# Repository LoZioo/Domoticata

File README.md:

# Domoticata
Custom domotic home system.

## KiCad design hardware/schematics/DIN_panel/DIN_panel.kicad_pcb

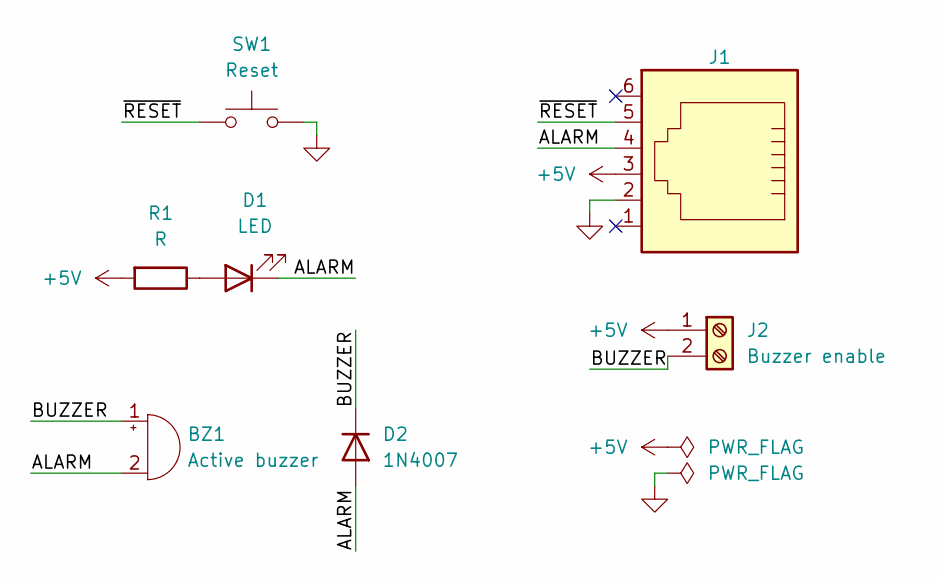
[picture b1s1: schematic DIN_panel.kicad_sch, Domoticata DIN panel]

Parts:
BZ1: Active buzzer; Buzzer_12x9.5RM7.6
D1: LED; LED_D5.0mm
D2: 1N4007; D_DO-41_SOD81_P7.62mm_Horizontal
J1: 6P6C; RJ25_Wayconn_MJEA-660X1_Horizontal
J2: Buzzer enable; TerminalBlock_4Ucon_1x02_P3.50mm_Horizontal
R1: R; R_Axial_DIN0207_L6.3mm_D2.5mm_P7.62mm_Horizontal
SW1: Reset; SW_PUSH_6mm_H5mm

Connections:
+5V: J1.3, J2.1, R1.2
/ALARM: BZ1.2 (-), D1.1 (K), D2.2 (A), J1.4
/BUZZER: BZ1.1 (+), D2.1 (K), J2.2
/~RESET: J1.5, SW1.1
GND: J1.2, SW1.2
unnamed: D1.2 (A), R1.1

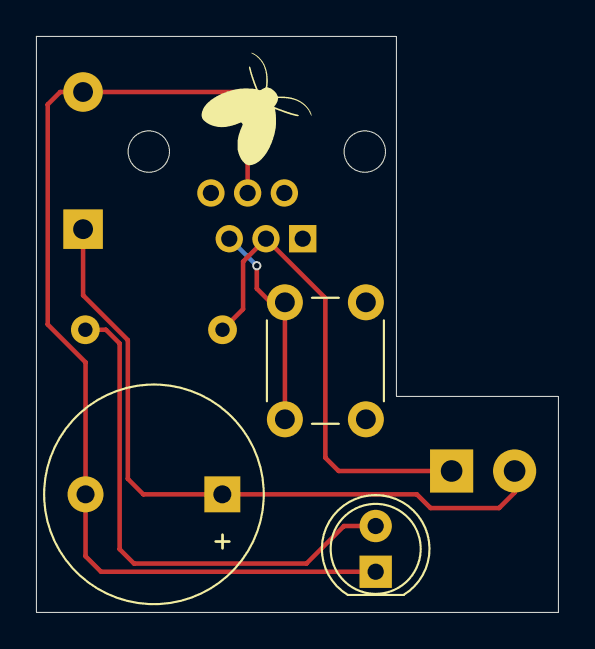
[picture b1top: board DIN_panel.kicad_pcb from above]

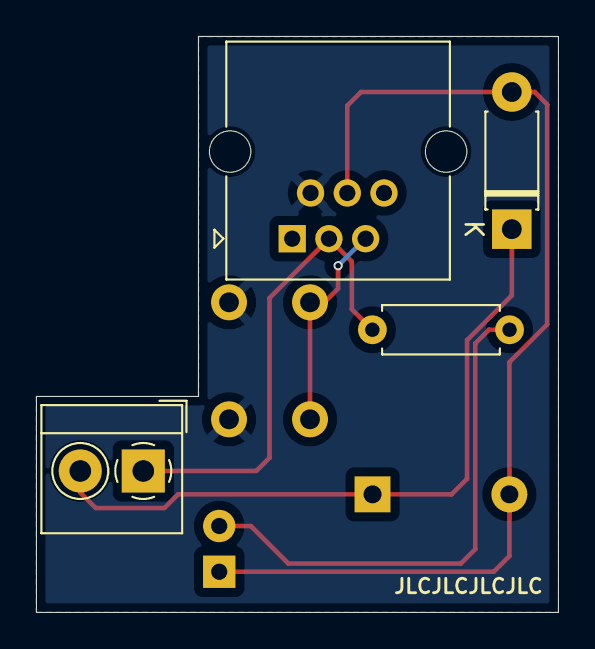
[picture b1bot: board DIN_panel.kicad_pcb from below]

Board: 2 copper layers, 29.0 x 32.0 mm, 7 parts (4 on the bottom side), 6 nets.

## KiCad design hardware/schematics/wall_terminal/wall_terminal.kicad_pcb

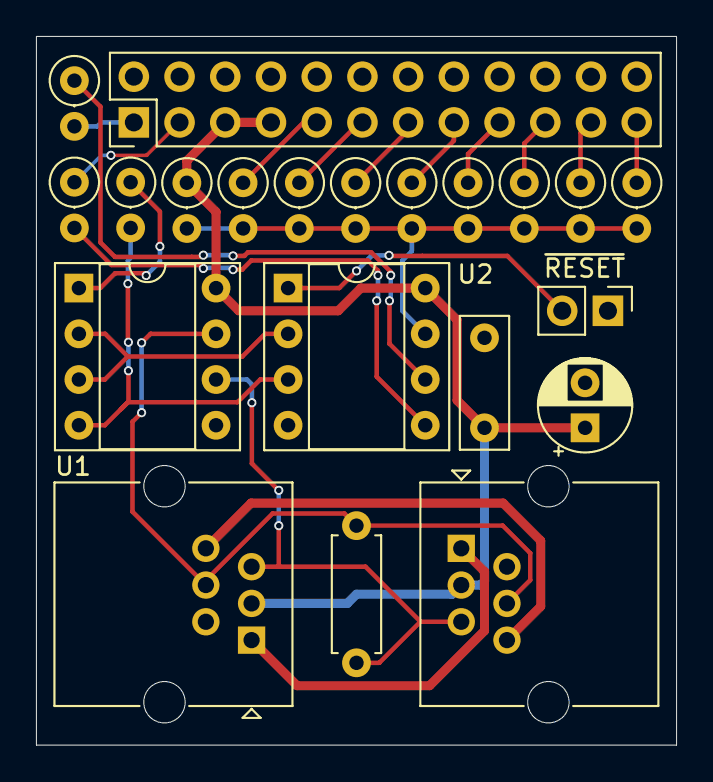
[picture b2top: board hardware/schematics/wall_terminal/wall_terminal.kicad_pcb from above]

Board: 2 copper layers, 35.6 x 39.4 mm, 21 parts (0 on the bottom side), 23 nets.

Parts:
C1: 10uF; CP_Radial_D5.0mm_P2.50mm
C2: 100nF; C_Rect_L7.2mm_W2.5mm_P5.00mm_FKS2_FKP2_MKS2_MKP2
J1: Reset; PinHeader_1x02_P2.54mm_Vertical
J2: Conn_02x12_Odd_Even; PinHeader_2x12_P2.54mm_Vertical
J3, J4: 6P6C; RJ25_Wayconn_MJEA-660X1_Horizontal
R1, R2, R3, R4, R5, R6, R7, R8, R9, R10, R11: R; R_Axial_DIN0207_L6.3mm_D2.5mm_P2.54mm_Vertical
R12: 1k; R_Axial_DIN0207_L6.3mm_D2.5mm_P2.54mm_Vertical
R13: 120; R_Axial_DIN0207_L6.3mm_D2.5mm_P7.62mm_Horizontal
U1: MAX487E; DIP-8_W7.62mm_Socket
U2: ATtiny13A-P; DIP-8_W7.62mm_Socket

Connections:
+5V: C1.1, C2.1, J2.5, J2.7, J3.3, J4.3, R11.1, U1.8 (VCC), U2.8 (VCC)
/BUS_SHORT_1: J3.1, J4.1
/BUS_SHORT_6: J3.6, J4.6
/IN/ADC: R3.2, R4.2, R5.2, R6.2, R7.2, R8.2, R9.2, R10.2, R11.2, U2.7 (PB2)
/IN/S1: J2.23, R3.1
/IN/S2: J2.21, R4.1
/IN/S3: J2.19, R5.1
/IN/S4: J2.17, R6.1
/IN/S5: J2.15, R7.1
/IN/S6: J2.13, R8.1
/IN/S7: J2.11, R9.1
/IN/S8: J2.9, R10.1
/MCU/DE/~RE: U1.2 (~RE), U1.3 (DE), U2.2 (PB3)
/MCU/PWM_A: R1.2, U2.5 (PB0)
/MCU/PWM_B: R2.1, U2.6 (PB1)
/MCU/RX/TX: R12.2, U1.4 (DI), U2.3 (PB4)
/MCU/~RST: J1.2, U2.1 (~RESET/PB5)
/RS485_A: J3.5, J4.5, R13.1, U1.6 (A)
/RS485_B: J3.4, J4.4, R13.2, U1.7 (B)
GND: C1.2, C2.2, J1.1, J2.2, J2.4, J2.6, J2.8, J2.10, J2.12, J2.14, J2.16, J2.18, J2.20, J2.22, J2.24, J3.2, J4.2, U1.5 (GND), U2.4 (GND)
unnamed: J2.1, R2.2
unnamed: J2.3, R1.1
unnamed: R12.1, U1.1 (RO)

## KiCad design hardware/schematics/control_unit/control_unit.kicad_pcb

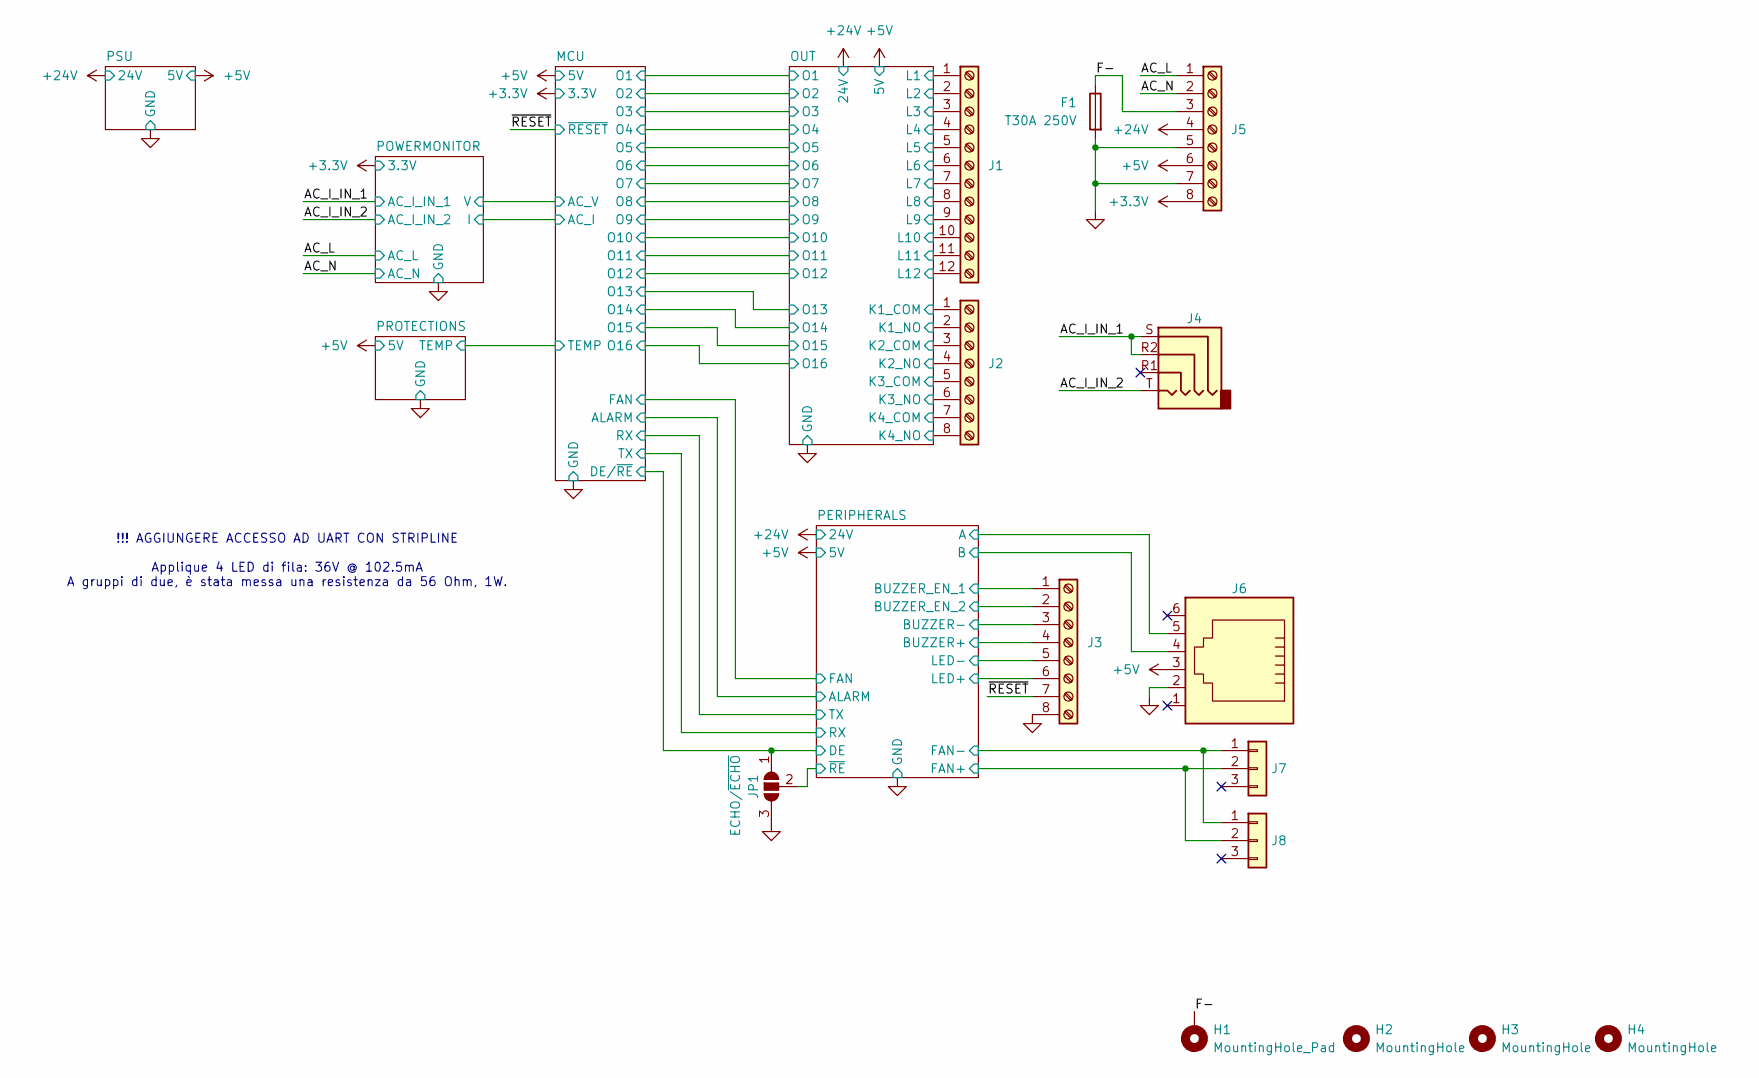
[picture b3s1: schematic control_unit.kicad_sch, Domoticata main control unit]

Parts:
F1: T30A 250V; Fuseholder_Clip-6.3x32mm_Littelfuse_102_Inline_P34.21x7.62m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
H1: MountingHole_Pad; MountingHole_4.5mm_Pad_TopBottom
H2, H3, H4: MountingHole; MountingHole_4.5mm_Pad_TopBottom
J1: Screw_Terminal_01x12; PhoenixContact_MCV_1,5_12-G-3.81_1x12_P3.81mm_D1.4mm_Vertic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
J2, J3, J5: Screw_Terminal_01x08; PhoenixContact_MCV_1,5_8-G-3.81_1x08_P3.81mm_D1.4mm_Vertical
J4: AudioJack4; SCT013
J6: 6P6C; RJ25_Wayconn_MJEA-660X1_Horizontal
J7, J8: Conn_01x03_Pin; FanPinHeader_1x03_P2.54mm_Vertical
JP1: ECHO/~{ECHO}; SolderJumper-3_P1.3mm_Open_Pad1.0x1.5mm

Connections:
+3.3V: J5.8; also elsewhere on the board
+5V: J3.4, J3.6, J5.6, J6.3; also elsewhere on the board
+24V: J5.4, J7.2, J8.2; also elsewhere on the board
/AC_I_IN_1: J4.R2, J4.S; also elsewhere on the board
/AC_I_IN_2: J4.T; also elsewhere on the board
/AC_L: J5.1; also elsewhere on the board
/AC_N: J5.2; also elsewhere on the board
/F-: F1.1, H1.1, J5.3
/MCU/DE/~RE: JP1.1 (A); also elsewhere on the board
/OUT/K1_COM: J2.1; also elsewhere on the board
/OUT/K1_NO: J2.2; also elsewhere on the board
/OUT/K2_COM: J2.3; also elsewhere on the board
/OUT/K2_NO: J2.4; also elsewhere on the board
/OUT/K3_COM: J2.5; also elsewhere on the board
/OUT/K3_NO: J2.6; also elsewhere on the board
/OUT/K4_COM: J2.7; also elsewhere on the board
/OUT/K4_NO: J2.8; also elsewhere on the board
/OUT/L1: J1.1; also elsewhere on the board
/OUT/L2: J1.2; also elsewhere on the board
/OUT/L3: J1.3; also elsewhere on the board
/OUT/L4: J1.4; also elsewhere on the board
/OUT/L5: J1.5; also elsewhere on the board
/OUT/L6: J1.6; also elsewhere on the board
/OUT/L7: J1.7; also elsewhere on the board
/OUT/L8: J1.8; also elsewhere on the board
/OUT/L9: J1.9; also elsewhere on the board
/OUT/L10: J1.10; also elsewhere on the board
/OUT/L11: J1.11; also elsewhere on the board
/OUT/L12: J1.12; also elsewhere on the board
/PERIPHERALS/A: J6.5; also elsewhere on the board
/PERIPHERALS/B: J6.4; also elsewhere on the board
/PERIPHERALS/BUZZER-: J3.1, J3.3
/PERIPHERALS/BUZZER_EN_2: J3.2; also elsewhere on the board
/PERIPHERALS/FAN-: J7.1, J8.1; also elsewhere on the board
/PERIPHERALS/LED-: J3.5; also elsewhere on the board
/PERIPHERALS/~RE: JP1.2 (C); also elsewhere on the board
/~RESET: J3.7; also elsewhere on the board
GND: F1.2, J3.8, J5.5, J5.7, J6.2, JP1.3 (B); also elsewhere on the board

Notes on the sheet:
!!! AGGIUNGERE ACCESSO AD UART CON STRIPLINE Applique 4 LED di fila: 36V @ 102.5mA A gruppi di due, è stata messa una resistenza da 56 Ohm, 1W.

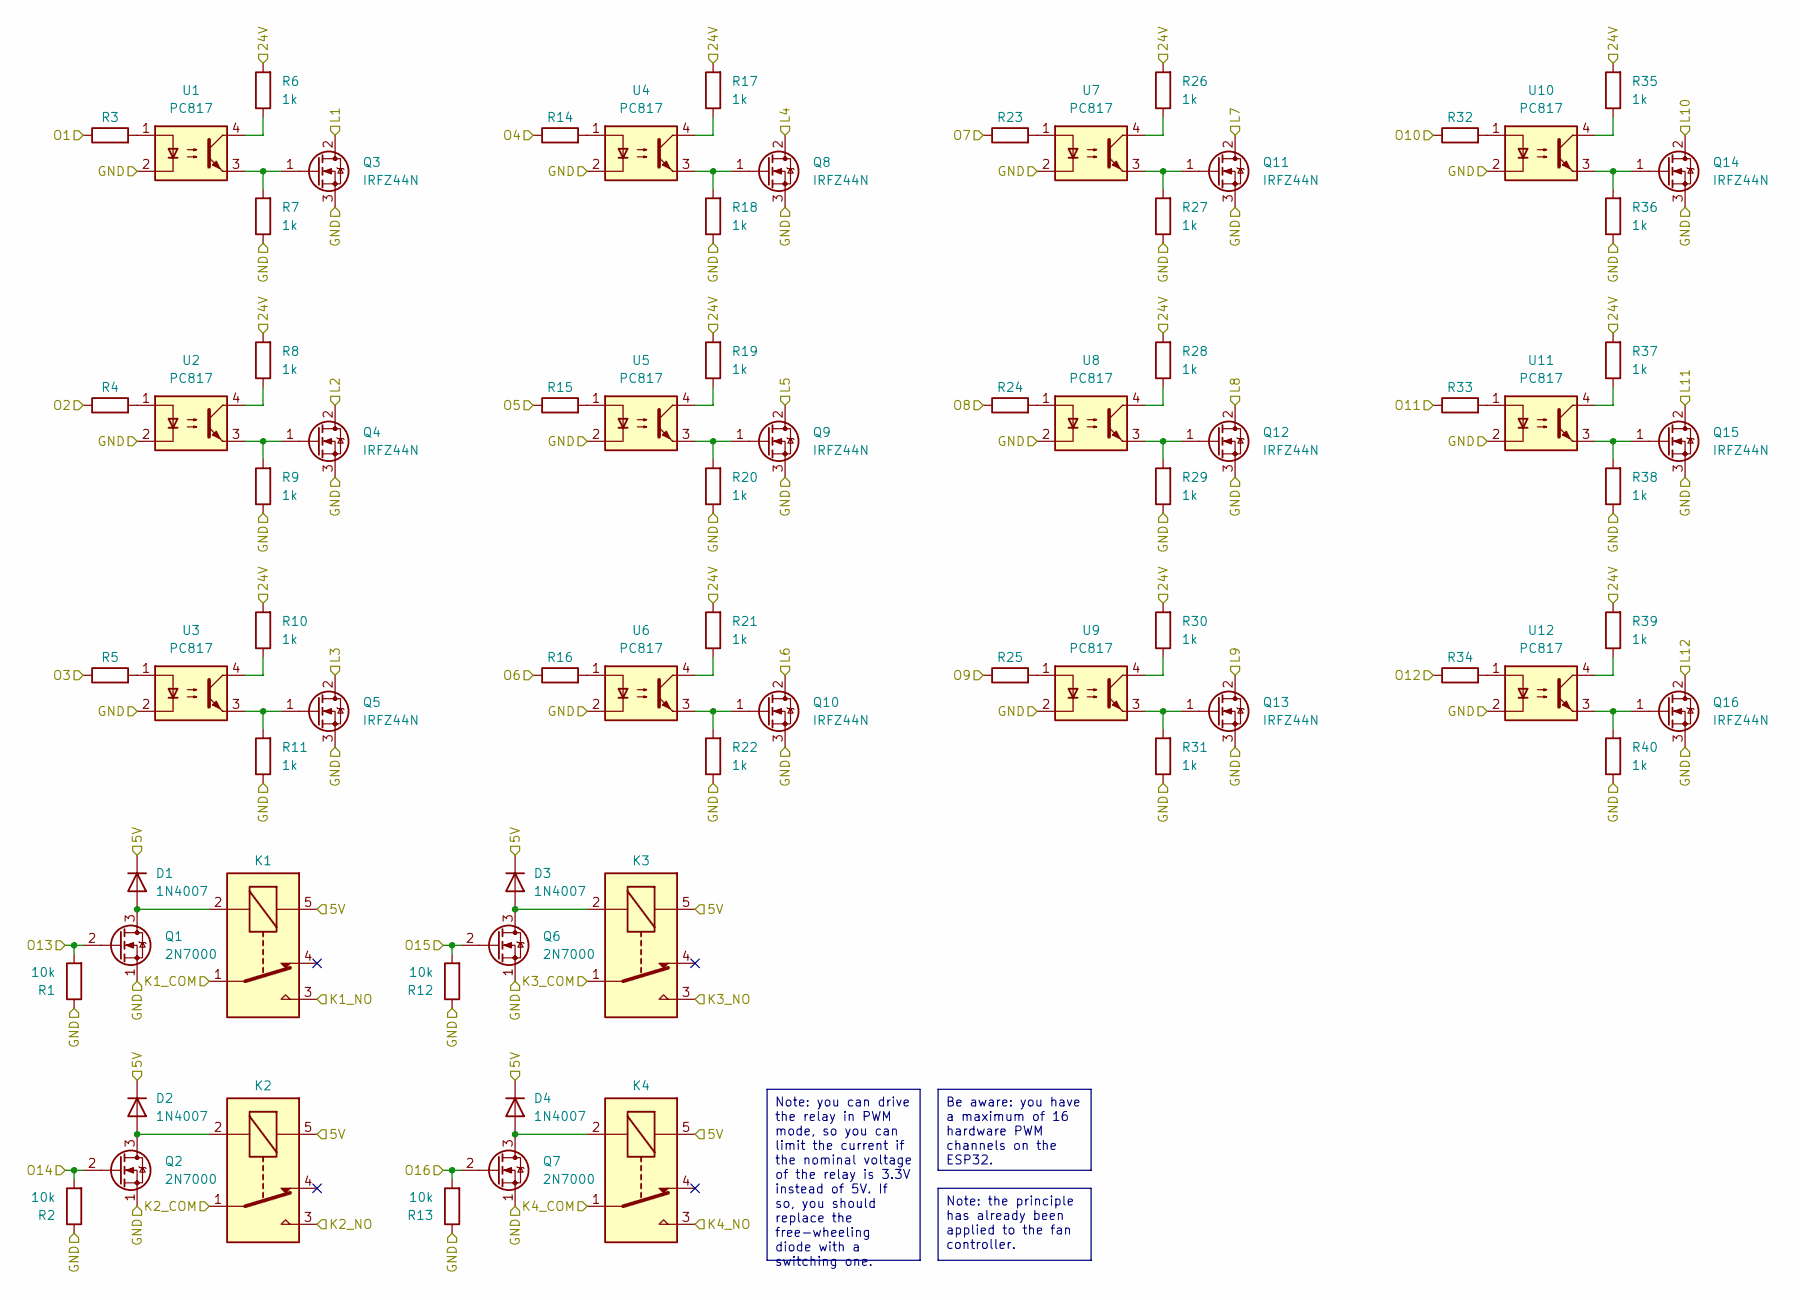
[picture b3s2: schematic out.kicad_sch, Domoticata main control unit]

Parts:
D1, D2, D3, D4: 1N4007; D_DO-41_SOD81_P7.62mm_Horizontal
K1, K2, K3, K4: Relay_SPDT; Relay_SPDT_Omron-G5LE-1
Q1, Q2, Q6, Q7: 2N7000; TO-92_Inline
Q3, Q4, Q5, Q8, Q9, Q10, Q11, Q12, Q13, Q14, Q15, Q16: IRFZ44N; TO-220-3_Vertical
R1, R2, R12, R13: 10k; R_Axial_DIN0207_L6.3mm_D2.5mm_P7.62mm_Horizontal
R3, R4, R5, R14, R15, R16, R23, R24, R25, R32, R33, R34: R; R_Axial_DIN0207_L6.3mm_D2.5mm_P7.62mm_Horizontal
R6, R7, R8, R9, R10, R11, R17, R18, R19, R20, R21, R22, R26, R27, R28, R29, R30, R31, R35, R36, R37, R38, R39, R40: 1k; R_Axial_DIN0207_L6.3mm_D2.5mm_P7.62mm_Horizontal
U1, U2, U3, U4, U5, U6, U7, U8, U9, U10, U11, U12: PC817; DIP-4_W7.62mm

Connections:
+5V: D1.1 (K), D2.1 (K), D3.1 (K), D4.1 (K), K1.5, K2.5, K3.5, K4.5; also elsewhere on the board
+24V: R6.2, R8.2, R10.2, R17.2, R19.2, R21.2, R26.2, R28.2, R30.2, R35.2, R37.2, R39.2; also elsewhere on the board
/MCU/O1: R3.1; also elsewhere on the board
/MCU/O2: R4.1; also elsewhere on the board
/MCU/O3: R5.1; also elsewhere on the board
/MCU/O4: R14.1; also elsewhere on the board
/MCU/O5: R15.1; also elsewhere on the board
/MCU/O6: R16.1; also elsewhere on the board
/MCU/O7: R23.1; also elsewhere on the board
/MCU/O8: R24.1; also elsewhere on the board
/MCU/O9: R25.1; also elsewhere on the board
/MCU/O10: R32.1; also elsewhere on the board
/MCU/O11: R33.1; also elsewhere on the board
/MCU/O12: R34.1; also elsewhere on the board
/MCU/O13: Q1.2 (G), R1.2; also elsewhere on the board
/MCU/O14: Q2.2 (G), R2.2; also elsewhere on the board
/MCU/O15: Q6.2 (G), R12.2; also elsewhere on the board
/MCU/O16: Q7.2 (G), R13.2; also elsewhere on the board
/OUT/K1_COM: K1.1; also elsewhere on the board
/OUT/K1_NO: K1.3; also elsewhere on the board
/OUT/K2_COM: K2.1; also elsewhere on the board
/OUT/K2_NO: K2.3; also elsewhere on the board
/OUT/K3_COM: K3.1; also elsewhere on the board
/OUT/K3_NO: K3.3; also elsewhere on the board
/OUT/K4_COM: K4.1; also elsewhere on the board
/OUT/K4_NO: K4.3; also elsewhere on the board
/OUT/L1: Q3.2 (D); also elsewhere on the board
/OUT/L2: Q4.2 (D); also elsewhere on the board
/OUT/L3: Q5.2 (D); also elsewhere on the board
/OUT/L4: Q8.2 (D); also elsewhere on the board
/OUT/L5: Q9.2 (D); also elsewhere on the board
/OUT/L6: Q10.2 (D); also elsewhere on the board
/OUT/L7: Q11.2 (D); also elsewhere on the board
/OUT/L8: Q12.2 (D); also elsewhere on the board
/OUT/L9: Q13.2 (D); also elsewhere on the board
/OUT/L10: Q14.2 (D); also elsewhere on the board
/OUT/L11: Q15.2 (D); also elsewhere on the board
/OUT/L12: Q16.2 (D); also elsewhere on the board
GND: Q1.1 (S), Q2.1 (S), Q3.3 (S), Q4.3 (S), Q5.3 (S), Q6.1 (S), Q7.1 (S), Q8.3 (S), Q9.3 (S), Q10.3 (S), Q11.3 (S), Q12.3 (S), Q13.3 (S), Q14.3 (S), Q15.3 (S), Q16.3 (S), R1.1, R2.1, R7.1, R9.1, R11.1, R12.1, R13.1, R18.1, R20.1, R22.1, R27.1, R29.1, R31.1, R36.1, R38.1, R40.1, U1.2, U2.2, U3.2, U4.2, U5.2, U6.2, U7.2, U8.2, U9.2, U10.2, U11.2, U12.2; also elsewhere on the board
unnamed: D1.2 (A), K1.2, Q1.3 (D)
unnamed: D2.2 (A), K2.2, Q2.3 (D)
unnamed: D3.2 (A), K3.2, Q6.3 (D)
unnamed: D4.2 (A), K4.2, Q7.3 (D)
unnamed: Q3.1 (G), R7.2, U1.3
unnamed: Q4.1 (G), R9.2, U2.3
unnamed: Q5.1 (G), R11.2, U3.3
unnamed: Q8.1 (G), R18.2, U4.3
unnamed: Q9.1 (G), R20.2, U5.3
unnamed: Q10.1 (G), R22.2, U6.3
unnamed: Q11.1 (G), R27.2, U7.3
unnamed: Q12.1 (G), R29.2, U8.3
unnamed: Q13.1 (G), R31.2, U9.3
unnamed: Q14.1 (G), R36.2, U10.3
unnamed: Q15.1 (G), R38.2, U11.3
unnamed: Q16.1 (G), R40.2, U12.3
unnamed: R3.2, U1.1
unnamed: R4.2, U2.1
unnamed: R5.2, U3.1
unnamed: R6.1, U1.4
unnamed: R8.1, U2.4
unnamed: R10.1, U3.4
unnamed: R14.2, U4.1
unnamed: R15.2, U5.1
unnamed: R16.2, U6.1
unnamed: R17.1, U4.4
unnamed: R19.1, U5.4
unnamed: R21.1, U6.4
unnamed: R23.2, U7.1
unnamed: R24.2, U8.1
unnamed: R25.2, U9.1
unnamed: R26.1, U7.4
unnamed: R28.1, U8.4
unnamed: R30.1, U9.4
unnamed: R32.2, U10.1
unnamed: R33.2, U11.1
unnamed: R34.2, U12.1
unnamed: R35.1, U10.4
unnamed: R37.1, U11.4
unnamed: R39.1, U12.4

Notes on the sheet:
Note: you can drive the relay in PWM mode, so you can limit the current if the nominal voltage of the relay is 3.3V instead of 5V. If so, you should replace the free-wheeling diode with a switching one.
Be aware: you have a maximum of 16 hardware PWM channels on the ESP32.
Note: the principle has already been applied to the fan controller.

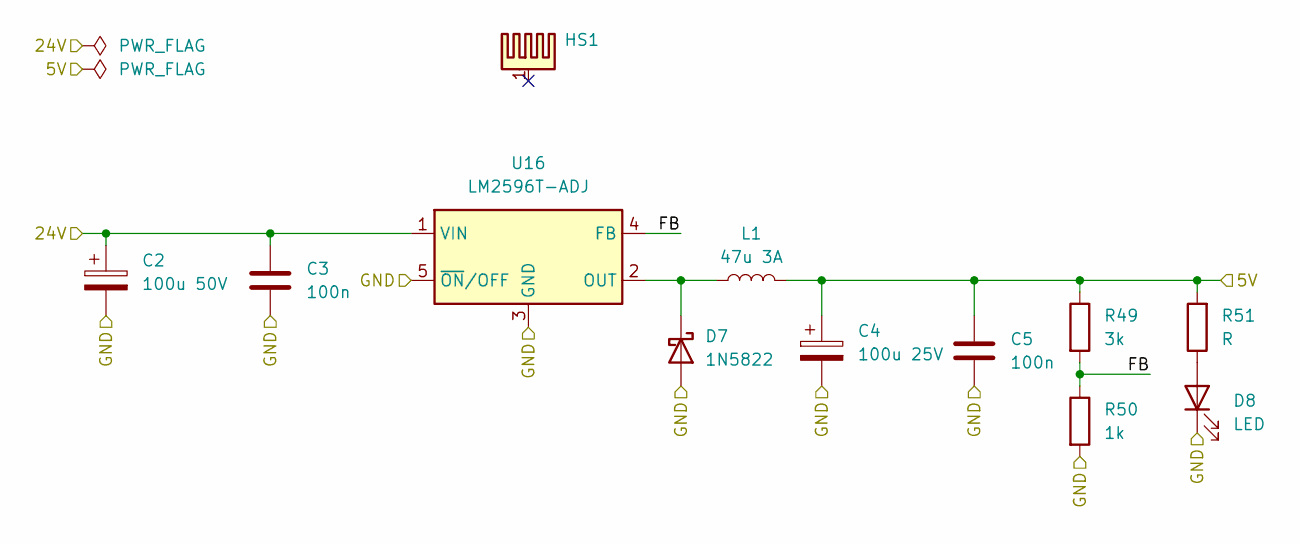
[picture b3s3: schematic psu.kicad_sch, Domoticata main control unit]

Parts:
C2: 100u 50V; CP_Radial_D8.0mm_P3.80mm
C3, C5: 100n; C_Rect_L7.2mm_W2.5mm_P5.00mm_FKS2_FKP2_MKS2_MKP2
C4: 100u 25V; CP_Radial_D6.3mm_P2.50mm
D7: 1N5822; D_DO-201AD_P12.70mm_Horizontal
D8: LED; LED_D5.0mm
HS1: Heatsink_Pad; Heatsink_Custom_1
L1: 47u 3A; L_Toroid_Vertical_L14.7mm_W8.6mm_P5.58mm_Pulse_KM-1
R49: 3k; R_Axial_DIN0207_L6.3mm_D2.5mm_P7.62mm_Horizontal
R50: 1k; R_Axial_DIN0207_L6.3mm_D2.5mm_P7.62mm_Horizontal
R51: R; R_Axial_DIN0207_L6.3mm_D2.5mm_P7.62mm_Horizontal
U16: LM2596T-ADJ; TO-220-5_Vertical

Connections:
+5V: C4.1, C5.1, L1.2, R49.1, R51.2; also elsewhere on the board
+24V: C2.1, C3.1, U16.1 (VIN); also elsewhere on the board
/PSU/FB: R49.2, R50.1, U16.4 (FB)
GND: C2.2, C3.2, C4.2, C5.2, D7.2 (A), D8.1 (K), R50.2, U16.3 (GND), U16.5 (~ON/OFF); also elsewhere on the board
unnamed: D7.1 (K), L1.1, U16.2 (OUT)
unnamed: D8.2 (A), R51.1

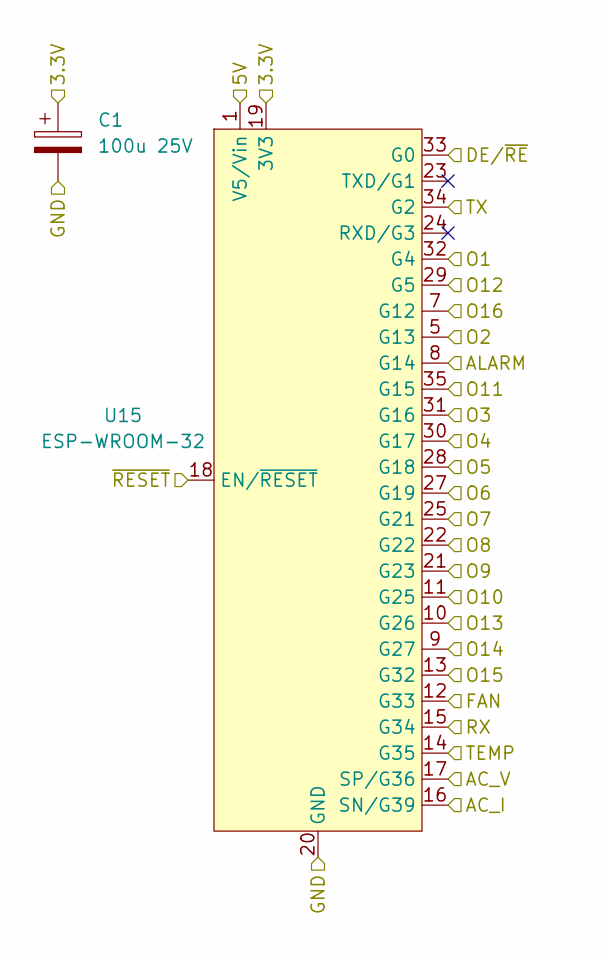
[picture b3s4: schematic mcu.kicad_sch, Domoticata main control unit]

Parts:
C1: 100u 25V; CP_Radial_D6.3mm_P2.50mm
U15: ESP-WROOM-32; ESP32_38PIN

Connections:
+3.3V: C1.1, U15.19 (3V3); also elsewhere on the board
+5V: U15.1 (V5/Vin); also elsewhere on the board
/MCU/AC_I: U15.16 (SN/G39); also elsewhere on the board
/MCU/AC_V: U15.17 (SP/G36); also elsewhere on the board
/MCU/ALARM: U15.8 (G14); also elsewhere on the board
/MCU/DE/~RE: U15.33 (G0); also elsewhere on the board
/MCU/FAN: U15.12 (G33); also elsewhere on the board
/MCU/O1: U15.32 (G4); also elsewhere on the board
/MCU/O2: U15.5 (G13); also elsewhere on the board
/MCU/O3: U15.31 (G16); also elsewhere on the board
/MCU/O4: U15.30 (G17); also elsewhere on the board
/MCU/O5: U15.28 (G18); also elsewhere on the board
/MCU/O6: U15.27 (G19); also elsewhere on the board
/MCU/O7: U15.25 (G21); also elsewhere on the board
/MCU/O8: U15.22 (G22); also elsewhere on the board
/MCU/O9: U15.21 (G23); also elsewhere on the board
/MCU/O10: U15.11 (G25); also elsewhere on the board
/MCU/O11: U15.35 (G15); also elsewhere on the board
/MCU/O12: U15.29 (G5); also elsewhere on the board
/MCU/O13: U15.10 (G26); also elsewhere on the board
/MCU/O14: U15.9 (G27); also elsewhere on the board
/MCU/O15: U15.13 (G32); also elsewhere on the board
/MCU/O16: U15.7 (G12); also elsewhere on the board
/MCU/RX: U15.15 (G34); also elsewhere on the board
/MCU/TEMP: U15.14 (G35); also elsewhere on the board
/MCU/TX: U15.34 (G2); also elsewhere on the board
/~RESET: U15.18 (EN/~RESET); also elsewhere on the board
GND: C1.2, U15.6 (GND), U15.20 (GND), U15.26 (GND); also elsewhere on the board

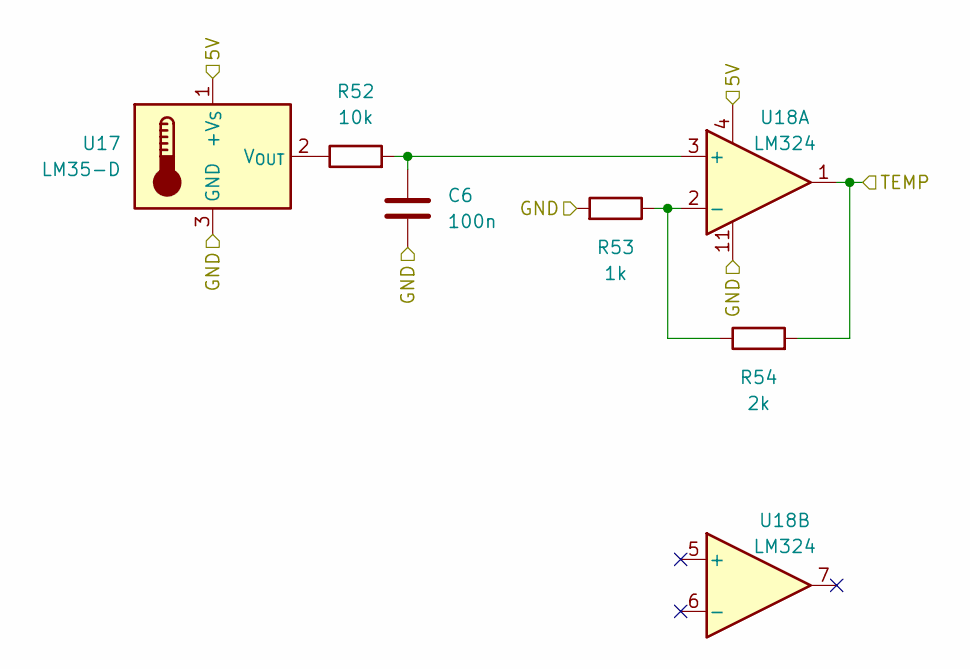
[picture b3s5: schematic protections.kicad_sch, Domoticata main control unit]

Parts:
C6: 100n; C_Rect_L7.2mm_W2.5mm_P5.00mm_FKS2_FKP2_MKS2_MKP2
R52: 10k; R_Axial_DIN0207_L6.3mm_D2.5mm_P7.62mm_Horizontal
R53: 1k; R_Axial_DIN0207_L6.3mm_D2.5mm_P7.62mm_Horizontal
R54: 2k; R_Axial_DIN0207_L6.3mm_D2.5mm_P7.62mm_Horizontal
U17: LM35-D; TO-92_Inline
U18: LM324; DIP-14_W7.62mm_Socket

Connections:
+5V: U17.1 (+V_{S}), U18.4 (V+); also elsewhere on the board
/MCU/TEMP: R54.2, U18.1; also elsewhere on the board
GND: C6.2, R53.2, U17.3 (GND), U18.11 (V-); also elsewhere on the board
unnamed: R52.1, U17.2 (V_{OUT})
unnamed: C6.1, R52.2, U18.3 (+)
unnamed: R53.1, R54.1, U18.2 (-)

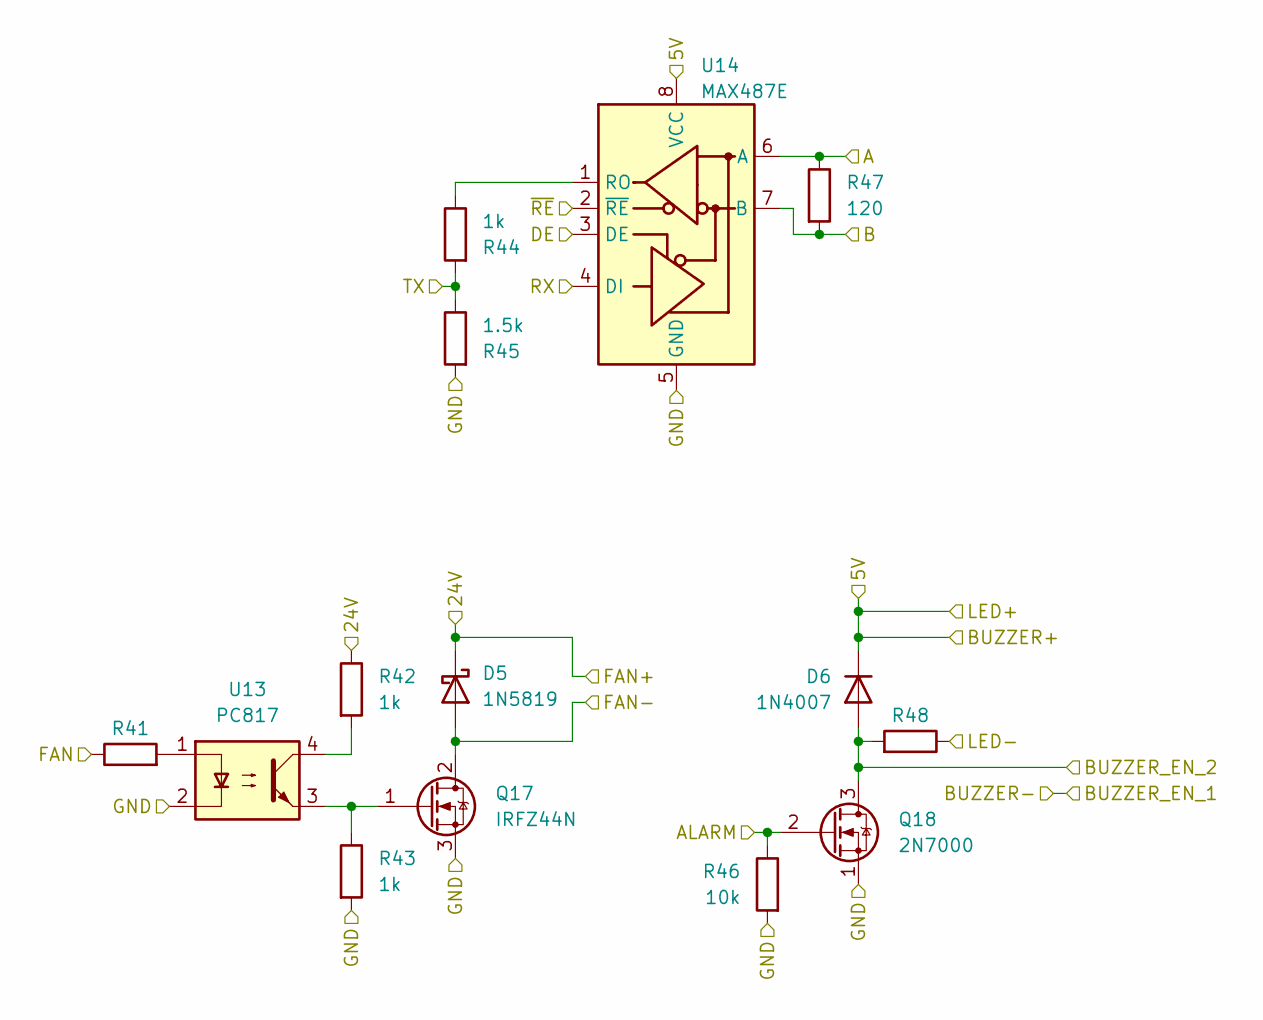
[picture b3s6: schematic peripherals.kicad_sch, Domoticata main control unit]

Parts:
D5: 1N5819; D_DO-41_SOD81_P7.62mm_Horizontal
D6: 1N4007; D_DO-41_SOD81_P7.62mm_Horizontal
Q17: IRFZ44N; TO-220-3_Vertical
Q18: 2N7000; TO-92_Inline
R41, R48: R; R_Axial_DIN0207_L6.3mm_D2.5mm_P7.62mm_Horizontal
R42, R43, R44: 1k; R_Axial_DIN0207_L6.3mm_D2.5mm_P7.62mm_Horizontal
R45: 1.5k; R_Axial_DIN0207_L6.3mm_D2.5mm_P7.62mm_Horizontal
R46: 10k; R_Axial_DIN0207_L6.3mm_D2.5mm_P7.62mm_Horizontal
R47: 120; R_Axial_DIN0207_L6.3mm_D2.5mm_P7.62mm_Horizontal
U13: PC817; DIP-4_W7.62mm
U14: MAX487E; DIP-8_W7.62mm_Socket

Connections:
+5V: D6.1 (K), U14.8 (VCC); also elsewhere on the board
+24V: D5.1 (K), R42.1; also elsewhere on the board
/MCU/ALARM: Q18.2 (G), R46.1; also elsewhere on the board
/MCU/DE/~RE: U14.3 (DE); also elsewhere on the board
/MCU/FAN: R41.1; also elsewhere on the board
/MCU/RX: R44.2, R45.1; also elsewhere on the board
/MCU/TX: U14.4 (DI); also elsewhere on the board
/PERIPHERALS/A: R47.1, U14.6 (A); also elsewhere on the board
/PERIPHERALS/B: R47.2, U14.7 (B); also elsewhere on the board
/PERIPHERALS/BUZZER_EN_2: D6.2 (A), Q18.3 (D), R48.2; also elsewhere on the board
/PERIPHERALS/FAN-: D5.2 (A), Q17.2 (D); also elsewhere on the board
/PERIPHERALS/LED-: R48.1; also elsewhere on the board
/PERIPHERALS/~RE: U14.2 (~RE); also elsewhere on the board
GND: Q17.3 (S), Q18.1 (S), R43.2, R45.2, R46.2, U13.2, U14.5 (GND); also elsewhere on the board
unnamed: Q17.1 (G), R43.1, U13.3
unnamed: R41.2, U13.1
unnamed: R42.2, U13.4
unnamed: R44.1, U14.1 (RO)

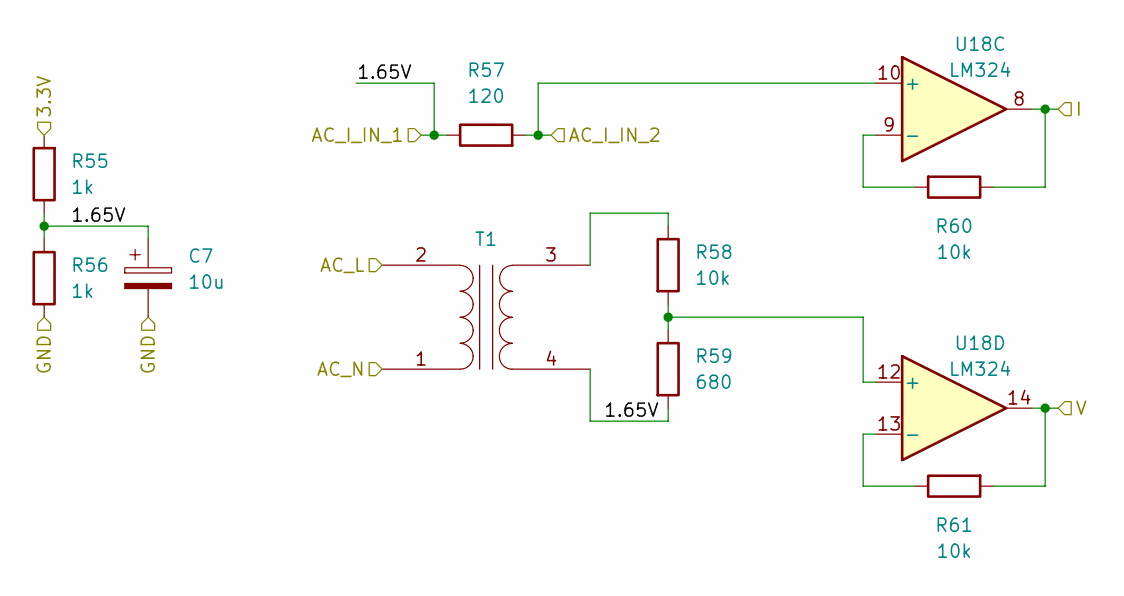
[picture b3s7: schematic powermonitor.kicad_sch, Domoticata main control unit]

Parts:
C7: 10u; CP_Radial_D4.0mm_P2.00mm
R55, R56: 1k; R_Axial_DIN0207_L6.3mm_D2.5mm_P7.62mm_Horizontal
R57: 120; R_Axial_DIN0207_L6.3mm_D2.5mm_P7.62mm_Horizontal
R58, R60, R61: 10k; R_Axial_DIN0207_L6.3mm_D2.5mm_P7.62mm_Horizontal
R59: 680; R_Axial_DIN0207_L6.3mm_D2.5mm_P7.62mm_Horizontal
T1: Transformer_1P_1S; Transformer
U18: LM324; DIP-14_W7.62mm_Socket

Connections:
+3.3V: R55.2; also elsewhere on the board
/AC_I_IN_1: C7.1, R55.1, R56.1, R57.1, R59.2, T1.4 (SB); also elsewhere on the board
/AC_I_IN_2: R57.2, U18.10 (+); also elsewhere on the board
/AC_L: T1.2 (AB); also elsewhere on the board
/AC_N: T1.1 (AA); also elsewhere on the board
/MCU/AC_I: R60.1, U18.8; also elsewhere on the board
/MCU/AC_V: R61.2, U18.14; also elsewhere on the board
GND: C7.2, R56.2; also elsewhere on the board
unnamed: R58.1, T1.3 (SA)
unnamed: R60.2, U18.9 (-)
unnamed: R58.2, R59.1, U18.12 (+)
unnamed: R61.1, U18.13 (-)

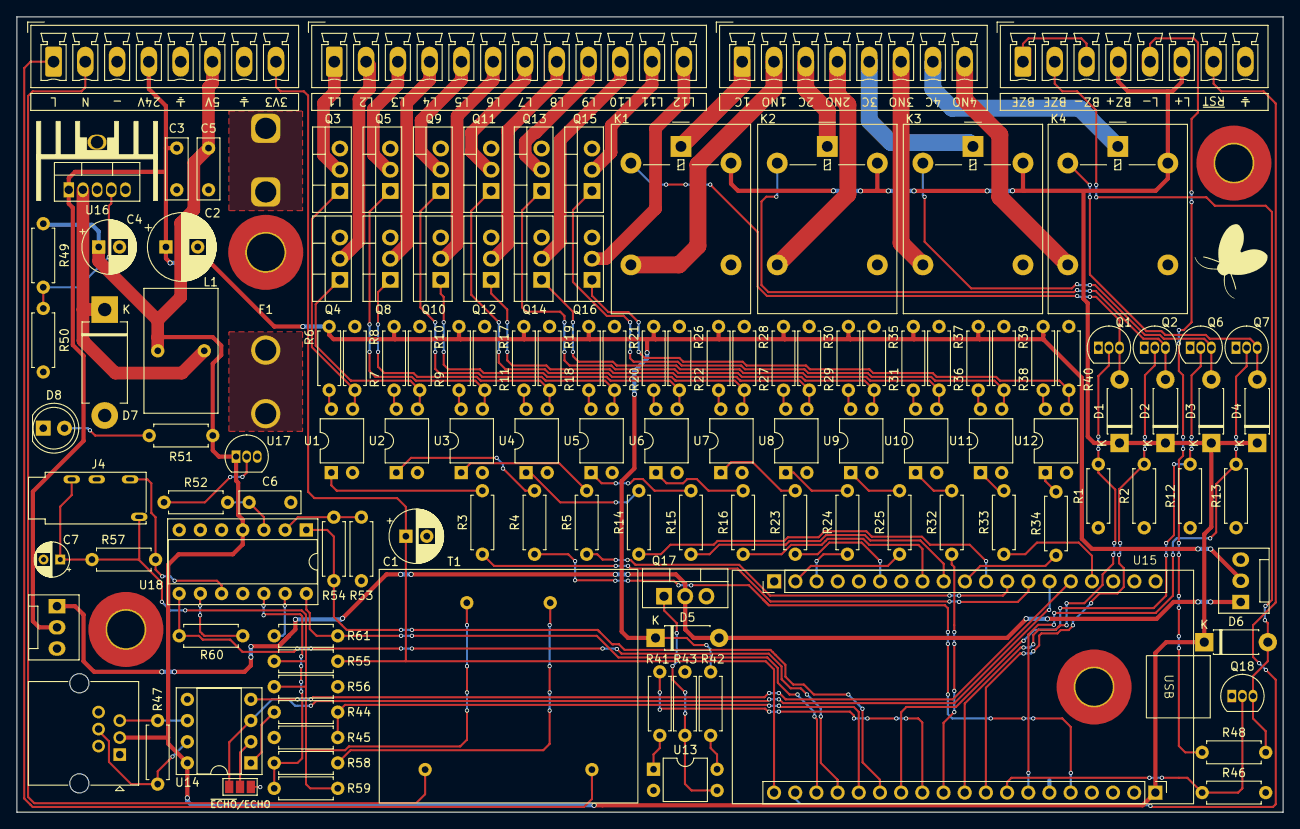
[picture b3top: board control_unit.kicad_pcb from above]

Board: 2 copper layers, 151.8 x 95.4 mm, 133 parts (0 on the bottom side), 115 nets.

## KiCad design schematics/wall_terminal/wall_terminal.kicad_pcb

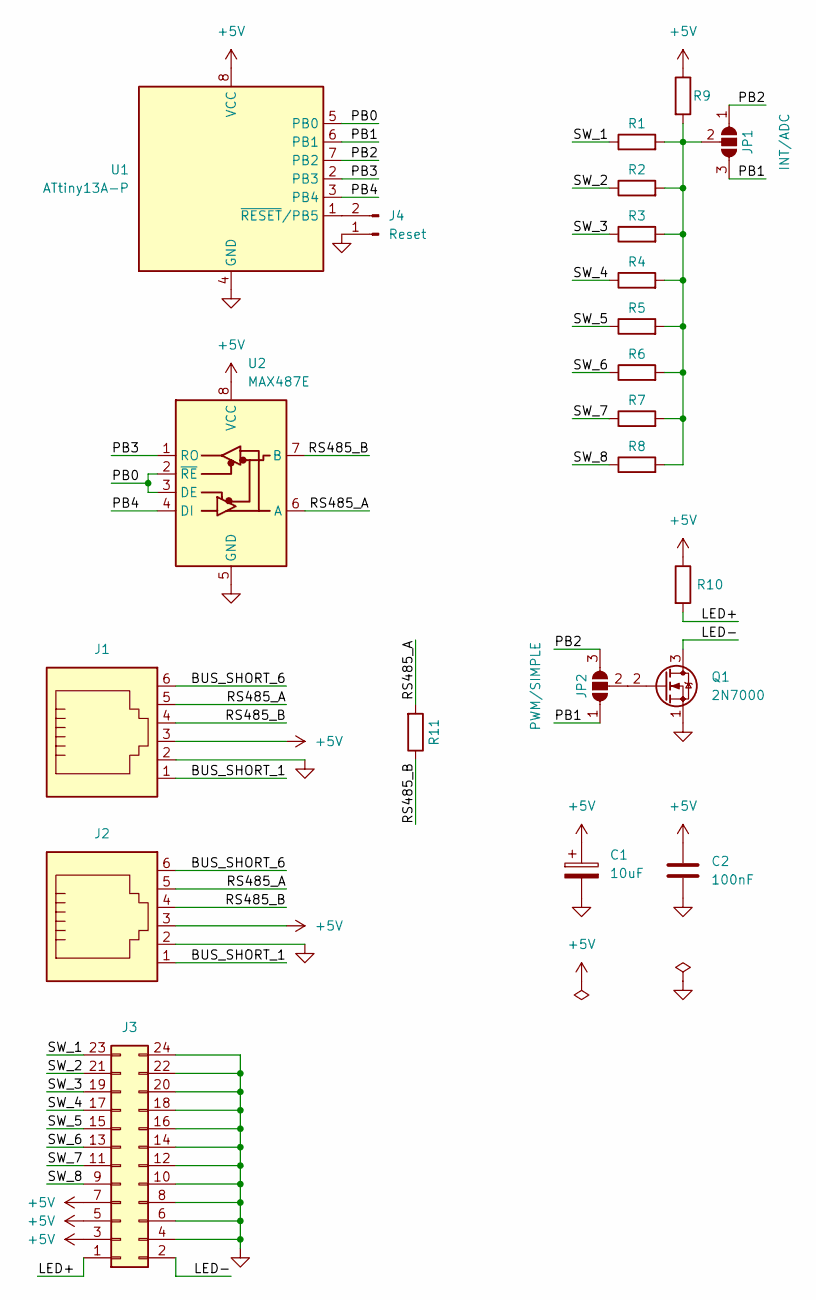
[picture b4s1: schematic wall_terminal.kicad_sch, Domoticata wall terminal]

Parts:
C1: 10uF; CP_Radial_D5.0mm_P2.50mm
C2: 100nF; C_Rect_L7.2mm_W2.5mm_P5.00mm_FKS2_FKP2_MKS2_MKP2
J1, J2: 6P6C; RJ25_Wayconn_MJEA-660X1_Horizontal
J3: Conn_02x12_Odd_Even; PinHeader_2x12_P2.54mm_Vertical
J4: Reset; PinHeader_1x02_P2.54mm_Vertical
JP1: INT/ADC; SolderJumper-3_P1.3mm_Open_Pad1.0x1.5mm
JP2: PWM/SIMPLE; SolderJumper-3_P1.3mm_Open_Pad1.0x1.5mm
Q1: 2N7000; TO-92_Inline
R1, R2, R3, R4, R5, R6, R7, R8, R9, R10: R; R_Axial_DIN0207_L6.3mm_D2.5mm_P2.54mm_Vertical
R11: R; R_Axial_DIN0207_L6.3mm_D2.5mm_P7.62mm_Horizontal
U1: ATtiny13A-P; DIP-8_W7.62mm_Socket
U2: MAX487E; DIP-8_W7.62mm_Socket

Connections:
+5V: C1.1, C2.1, J1.3, J2.3, J3.3, J3.5, J3.7, R9.1, R10.1, U1.8 (VCC), U2.8 (VCC)
/BUS_SHORT_1: J1.1, J2.1
/BUS_SHORT_6: J1.6, J2.6
/LED+: J3.1, R10.2
/LED-: J3.2, Q1.3 (D)
/PB0: U1.5 (PB0), U2.2 (~RE), U2.3 (DE)
/PB1: JP1.3 (B), JP2.1 (A), U1.6 (PB1)
/PB2: JP1.1 (A), JP2.3 (B), U1.7 (PB2)
/PB3: U1.2 (PB3), U2.1 (RO)
/PB4: U1.3 (PB4), U2.4 (DI)
/RS485_A: J1.5, J2.5, R11.2, U2.6 (A)
/RS485_B: J1.4, J2.4, R11.1, U2.7 (B)
/SW_1: J3.23, R1.1
/SW_2: J3.21, R2.1
/SW_3: J3.19, R3.1
/SW_4: J3.17, R4.1
/SW_5: J3.15, R5.1
/SW_6: J3.13, R6.1
/SW_7: J3.11, R7.1
/SW_8: J3.9, R8.1
GND: C1.2, C2.2, J1.2, J2.2, J3.4, J3.6, J3.8, J3.10, J3.12, J3.14, J3.16, J3.18, J3.20, J3.22, J3.24, J4.1, Q1.1 (S), U1.4 (GND), U2.5 (GND)
unnamed: J4.2, U1.1 (~RESET/PB5)
unnamed: JP1.2 (C), R1.2, R2.2, R3.2, R4.2, R5.2, R6.2, R7.2, R8.2, R9.2
unnamed: JP2.2 (C), Q1.2 (G)
